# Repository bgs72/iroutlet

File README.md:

# IrOutlet
IrOutlet is an 8-port power outlet. Each power outlet can be switched on or off using an IR remote.

## Design details
A [TSOP4836](KiCad/doc/tsop4836.pdf) IR receiver converts the IR light into a bit stream. This bit stream is decoded by a [PIC16F15325](KiCad/doc/pic16f15325.pdf) microcontroller.
When the IR signal is decoded, the microcontroller performs an action if the signal matches a supported IR address/command listed below:

| Address | Command    | Action                 |
|---------|------------| -----------------------|
| `0b00101` | `0b00000000` | Switch all outlets on  |
| `0b00101` | `0b00000001` | Switch outlet 1 on     |
| `0b00101` | `0b00000010` | Switch outlet 2 on     |
| `0b00101` | `0b00000011` | Switch outlet 3 on     |
| `0b00101` | `0b00000100` | Switch outlet 4 on     |
| `0b00101` | `0b00000101` | Switch outlet 5 on     |
| `0b00101` | `0b00000110` | Switch outlet 6 on     |
| `0b00101` | `0b00000111` | Switch outlet 7 on     |
| `0b00101` | `0b00001000` | Switch outlet 8 on     |
| `0b00101` | `0b00001001` | Switch all outlets off |
| `0b00101` | `0b00100000` | Switch outlet 1 off    |
| `0b00101` | `0b00100001` | Switch outlet 2 off    |
| `0b00101` | `0b00110010` | Switch outlet 3 off    |
| `0b00101` | `0b00110101` | Switch outlet 4 off    |
| `0b00101` | `0b00110100` | Switch outlet 5 off    |
| `0b00101` | `0b00110110` | Switch outlet 6 off    |
| `0b00101` | `0b00101001` | Switch outlet 7 off    |
| `0b00101` | `0b00111110` | Switch outlet 8 off    |

## Notes

1. Address `0b00101` corresponds to the address of a Marantz remote control I had available.

2. Below are some oscilloscope captures measured at the output pin of the [TSOP4836](KiCad/doc/tsop4836.pdf) while using the Marantz remote control:<br>

## Development tree

The project consists of three major folders:

1. [Mplab](https://www.microchip.com/en-us/tools-resources/develop/mplab-x-ide)
  
  This folder contains the bare-metal code for the Microchip [PIC16F15325](KiCad/doc/pic16f15325.pdf) controller.
  [MPLAB X IDE](https://www.microchip.com/en-us/tools-resources/develop/mplab-x-ide) or [VSCode](https://code.visualstudio.com/) with the MPLAB extension can be used as the development environment (using the free [XC8](https://www.microchip.com/en-us/tools-resources/develop/mplab-xc-compilers/xc8) compiler).
  
  Major implementation files:
  - [rc5.h](Mplab/IrOutlet.X/rc5.h): RC5 decoder API
  - [rc5.c](Mplab/IrOutlet.X/rc5.c): RC5 decoder implementation
  - [interrupts.c](Mplab/IrOutlet.X/interrupts.c): [TSOP4836](KiCad/doc/tsop4836.pdf) and timer interrupt handlers
  - [main.c](Mplab/IrOutlet.X/main.c): Controller setup and IR handling

2. [KiCad](https://www.kicad.org)
    
    This folder contains the IrOutlet schematic and PCB design.

    - The schematic consists of two major parts:
      1. The controller:<br>
        
      2. The relay driver:<br>
        
    - The components are laid out on a single-sided PCB:
      1. Component layout:<br>
        
      2. Bottom mask:<br>

3. [FreeCAD](https://www.freecad.org)

    This folder contains the 3D enclosure model for the IrOutlet.

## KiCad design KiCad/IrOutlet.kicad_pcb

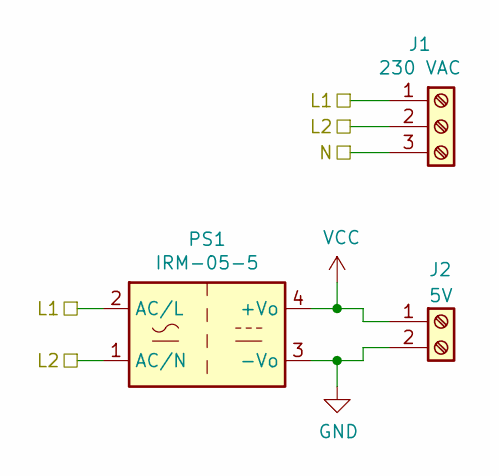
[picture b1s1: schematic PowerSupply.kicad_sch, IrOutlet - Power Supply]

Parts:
J1: 230 VAC; TB_1x3
J2: 5V; TB_1x2
PS1: IRM-05-5

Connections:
/PowerSupply/L1: J1.1, PS1.2 (AC/L); also elsewhere on the board
/PowerSupply/L2: J1.2, PS1.1 (AC/N); also elsewhere on the board
/PowerSupply/N: J1.3; also elsewhere on the board
GND: J2.2, PS1.3 (-Vo); also elsewhere on the board
VCC: J2.1, PS1.4 (+Vo); also elsewhere on the board

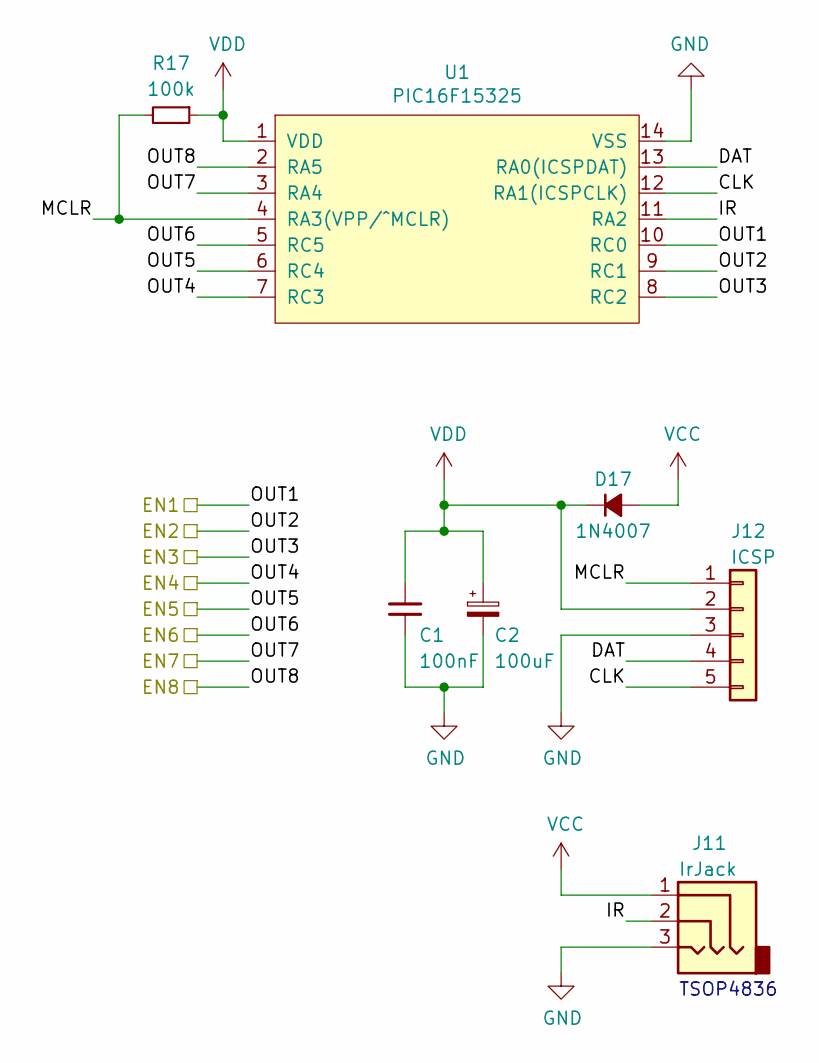
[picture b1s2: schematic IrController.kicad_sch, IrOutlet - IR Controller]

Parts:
C1: 100nF; C_L7.62mm_W3.2mm
C2: 100uF; CAP_6.3mm_P2.50mm
D17: 1N4007; DIODE_H
J11: IrJack; HDR_1x3
J12: ICSP; HDR_1x5
R17: 100k; RES_H
U1: PIC16F15325; DIP-14

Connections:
/IrController/CLK: J12.5, U1.12 (RA1(ICSPCLK))
/IrController/DAT: J12.4, U1.13 (RA0(ICSPDAT))
/IrController/IR: J11.2, U1.11 (RA2)
/IrController/MCLR: J12.1, R17.2, U1.4 (RA3(VPP/^MCLR))
/IrController/OUT1: U1.10 (RC0); also elsewhere on the board
/IrController/OUT2: U1.9 (RC1); also elsewhere on the board
/IrController/OUT3: U1.8 (RC2); also elsewhere on the board
/IrController/OUT4: U1.7 (RC3); also elsewhere on the board
/IrController/OUT5: U1.6 (RC4); also elsewhere on the board
/IrController/OUT6: U1.5 (RC5); also elsewhere on the board
/IrController/OUT7: U1.3 (RA4); also elsewhere on the board
/IrController/OUT8: U1.2 (RA5); also elsewhere on the board
GND: C1.2, C2.2, J11.3, J12.3, U1.14 (VSS); also elsewhere on the board
VCC: D17.2 (A), J11.1; also elsewhere on the board
VDD: C1.1, C2.1, D17.1 (K), J12.2, R17.1, U1.1 (VDD)

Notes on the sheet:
TSOP4836

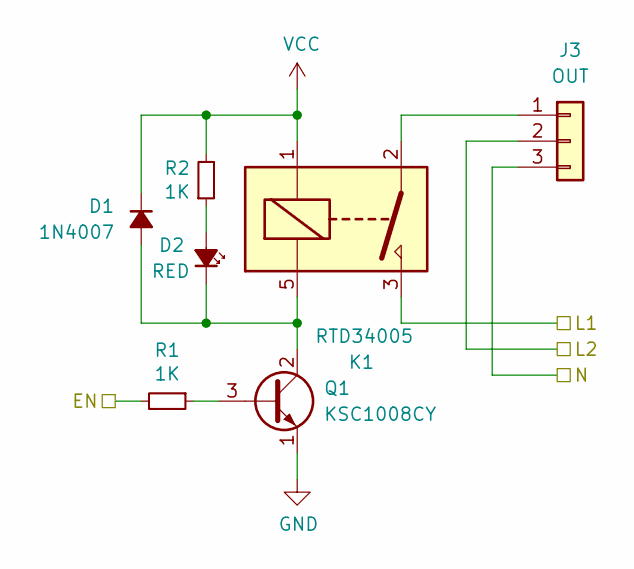
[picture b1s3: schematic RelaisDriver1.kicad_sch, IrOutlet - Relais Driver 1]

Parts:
D1: 1N4007; DIODE_H
D2: RED; HDR_1x2
J3: OUT; OUTLET
K1: RTD34005; RELAY_TE_RTD3405
Q1: KSC1008CY; TO-92
R1, R2: 1K; RES_H

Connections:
/IrController/OUT1: R1.2; also elsewhere on the board
/PowerSupply/L1: K1.3; also elsewhere on the board
/PowerSupply/L2: J3.2; also elsewhere on the board
/PowerSupply/N: J3.3; also elsewhere on the board
GND: Q1.1 (E); also elsewhere on the board
unnamed: D1.2 (A), D2.1 (K), K1.5, Q1.2 (C)
unnamed: D2.2 (A), R2.1
unnamed: J3.1, K1.2
unnamed: Q1.3 (B), R1.1
VCC: D1.1 (K), K1.1, R2.2; also elsewhere on the board

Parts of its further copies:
D3, D5, D7: 1N4007; DIODE_H
D4, D6, D8: RED; HDR_1x2
J4, J5, J6: OUT; OUTLET
K2, K3, K4: RTD34005; RELAY_TE_RTD3405
Q2, Q3, Q4: KSC1008CY; TO-92
R3, R4, R5, R6, R7, R8: 1K; RES_H

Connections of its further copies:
/IrController/OUT2: R3.2; also elsewhere on the board
/IrController/OUT3: R5.2; also elsewhere on the board
/IrController/OUT4: R7.2; also elsewhere on the board
/PowerSupply/L1: K2.3, K3.3, K4.3; also elsewhere on the board
/PowerSupply/L2: J4.2, J5.2, J6.2; also elsewhere on the board
/PowerSupply/N: J4.3, J5.3, J6.3; also elsewhere on the board
GND: Q2.1 (E), Q3.1 (E), Q4.1 (E); also elsewhere on the board
unnamed: D3.2 (A), D4.1 (K), K2.5, Q2.2 (C)
unnamed: D4.2 (A), R4.1
unnamed: D5.2 (A), D6.1 (K), K3.5, Q3.2 (C)
unnamed: D6.2 (A), R6.1
unnamed: D7.2 (A), D8.1 (K), K4.5, Q4.2 (C)
unnamed: D8.2 (A), R8.1
unnamed: J4.1, K2.2
unnamed: J5.1, K3.2
unnamed: J6.1, K4.2
unnamed: Q2.3 (B), R3.1
unnamed: Q3.3 (B), R5.1
unnamed: Q4.3 (B), R7.1
VCC: D3.1 (K), D5.1 (K), D7.1 (K), K2.1, K3.1, K4.1, R4.2, R6.2, R8.2; also elsewhere on the board

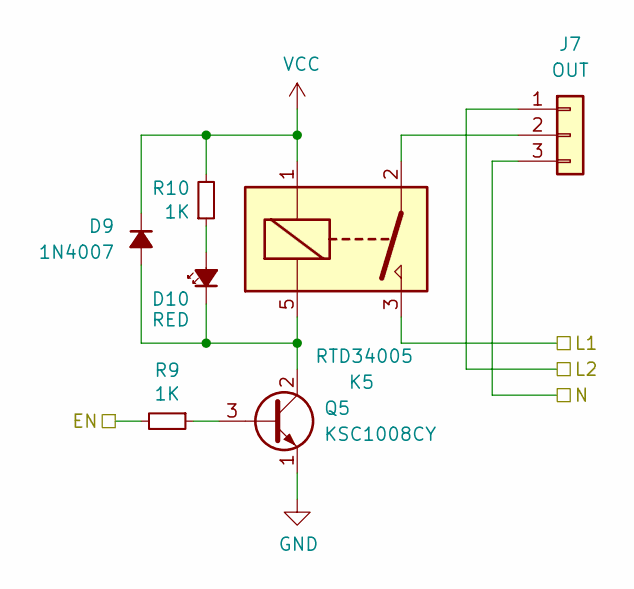
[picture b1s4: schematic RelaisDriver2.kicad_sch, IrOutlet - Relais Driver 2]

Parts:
D9: 1N4007; DIODE_H
D10: RED; HDR_1x2
J7: OUT; OUTLET
K5: RTD34005; RELAY_TE_RTD3405
Q5: KSC1008CY; TO-92
R9, R10: 1K; RES_H

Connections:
/IrController/OUT5: R9.2; also elsewhere on the board
/PowerSupply/L1: K5.3; also elsewhere on the board
/PowerSupply/L2: J7.1; also elsewhere on the board
/PowerSupply/N: J7.3; also elsewhere on the board
GND: Q5.1 (E); also elsewhere on the board
unnamed: D10.2 (A), R10.1
unnamed: D9.2 (A), D10.1 (K), K5.5, Q5.2 (C)
unnamed: J7.2, K5.2
unnamed: Q5.3 (B), R9.1
VCC: D9.1 (K), K5.1, R10.2; also elsewhere on the board

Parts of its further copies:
D11, D13, D15: 1N4007; DIODE_H
D12, D14, D16: RED; HDR_1x2
J8, J9, J10: OUT; OUTLET
K6, K7, K8: RTD34005; RELAY_TE_RTD3405
Q6, Q7, Q8: KSC1008CY; TO-92
R11, R12, R13, R14, R15, R16: 1K; RES_H

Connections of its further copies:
/IrController/OUT6: R11.2; also elsewhere on the board
/IrController/OUT7: R13.2; also elsewhere on the board
/IrController/OUT8: R15.2; also elsewhere on the board
/PowerSupply/L1: K6.3, K7.3, K8.3; also elsewhere on the board
/PowerSupply/L2: J8.1, J9.1, J10.1; also elsewhere on the board
/PowerSupply/N: J8.3, J9.3, J10.3; also elsewhere on the board
GND: Q6.1 (E), Q7.1 (E), Q8.1 (E); also elsewhere on the board
unnamed: D11.2 (A), D12.1 (K), K6.5, Q6.2 (C)
unnamed: D12.2 (A), R12.1
unnamed: D13.2 (A), D14.1 (K), K7.5, Q7.2 (C)
unnamed: D14.2 (A), R14.1
unnamed: D15.2 (A), D16.1 (K), K8.5, Q8.2 (C)
unnamed: D16.2 (A), R16.1
unnamed: J8.2, K6.2
unnamed: J9.2, K7.2
unnamed: J10.2, K8.2
unnamed: Q6.3 (B), R11.1
unnamed: Q7.3 (B), R13.1
unnamed: Q8.3 (B), R15.1
VCC: D11.1 (K), D13.1 (K), D15.1 (K), K6.1, K7.1, K8.1, R12.2, R14.2, R16.2; also elsewhere on the board

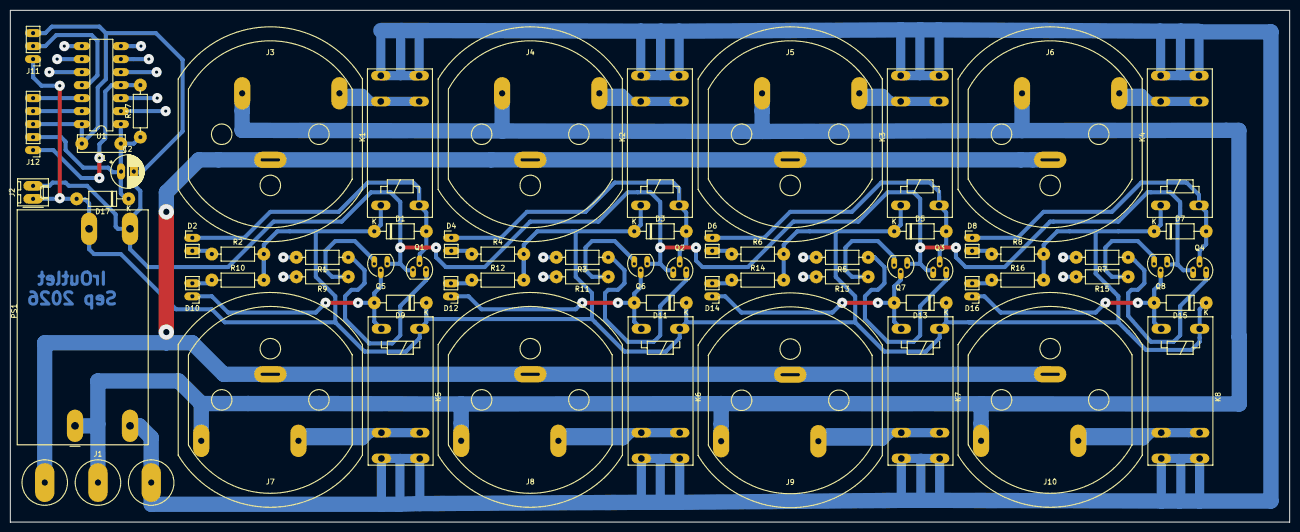
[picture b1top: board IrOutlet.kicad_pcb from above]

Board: 2 copper layers, 250.0 x 100.0 mm, 66 parts (0 on the bottom side), 50 nets.

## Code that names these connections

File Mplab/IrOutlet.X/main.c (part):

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#pragma config FCMEN = OFF          // Fail-Safe Clock Monitor Enable bit (FSCM timer disabled)

/*-- CONFIG2 --*/
#pragma config MCLRE = ON           // Master Clear Enable bit (MCLR pin is Master Clear function)
#pragma config PWRTE = OFF          // Power-up Timer Enable bit (PWRT disabled)
#pragma config LPBOREN = OFF        // Low-Power BOR enable bit (ULPBOR disabled)
#pragma config BOREN = OFF          // Brown-out reset enable bits (Brown-out reset disabled)
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                    case 0b0000001: /* '1' */
                    {
                        /*-- switch outlet 1 on --*/
                        PORTCbits.RC0 = 1;                        
                        break;
                    }

                    case 0b0000010: /* '2' */
                    {
                        /*-- swith outlet 2 on --*/
                        PORTCbits.RC1 = 1;
                        break;
                    }

                    case 0b0000011: /* '3' */
                    {
                        /*-- switch outlet 3 on --*/
                        PORTCbits.RC2 = 1;
                        break;
                    }

                    case 0b0000100: /* '4' */
                    {
                        /*-- switch outlet 4 on --*/
                        PORTCbits.RC3 = 1;
                        break;
                    }

                    case 0b0000101: /* '5' */
                    {
                        /*-- switch outlet 5 on --*/
                        PORTCbits.RC4 = 1;
                        break;
                    }
                    
                    case 0b0000110: /* '6' */
                    {
                        /*-- switch outlet 6 on --*/
                        PORTCbits.RC5 = 1;
                        break;
                    }

                    case 0b0000111: /* '7' */
                    {
                        /*-- switch outlet 7 on --*/
                        PORTAbits.RA4 = 1;
                        break;
                    }

                    case 0b0001000: /* '8' */
                    {
                        /*-- switch outlet 8 on --*/
                        PORTAbits.RA5 = 1;
                        break;
                    }

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                    case 0b00100000: /* 'PGM+' */
                    {
                        /*-- switch outlet 1 off --*/
                        PORTCbits.RC0 = 0;
                        break;
                    }

                    case 0b00100001: /* 'PGM-' */
                    {
                        /*-- switch outlet 2 off --*/
                        PORTCbits.RC1 = 0;
                        break;
                    }
                    
                    case 0b00110010: /* '<<' */
                    {
                        /*-- switch outlet 3 off --*/
                        PORTCbits.RC2 = 0;
                        break;
                    }

                    case 0b00110101: /* '>' */
                    {
                        /*-- switch outlet 4 off --*/
                        PORTCbits.RC3 = 0;
                        break;
                    }

                    case 0b00110100: /* '>>' */
                    {
                        /*-- switch outlet 5 off --*/
                        PORTCbits.RC4 = 0;
                        break;
                    }

                    case 0b00110110: /* '[]' */
                    {
                        /*-- switch outlet 6 off --*/
                        PORTCbits.RC5 = 0;
                        break;
                    }

                    case 0b00101001: /* '||' */
                    {
                        /*-- switch outlet 7 off --*/
                        PORTAbits.RA4 = 0;
                        break;
                    }

                    case 0b00111110: /* 'AV' */
                    {
                        /*-- switch outlet 8 off --*/
                        PORTAbits.RA5 = 0;
                        break;
                    }

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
